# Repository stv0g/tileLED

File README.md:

tileLED
=======

A very minimalistic driver for 8x8 LED dot matrix displays.

Based on an ATmega8 this board can drive a simple LED matrix displays. There is no real "driver" circuit on the board. We just use the GPIOs of the AVR mcu to sink/source the LED current.

According to the ATmega8 datasheet this usage is a bit out of spec, but tests with 3 Volt button cells were successful. Also 5 Volt supplies are okay.

The source code includes a simple demonstration application. Paired with a DS1820 digital temperature sensor, the display shows the current temperature and records the minimal and maximal temperature ever measured.

A Blog post on http://www.steffenvogel.de will follow.

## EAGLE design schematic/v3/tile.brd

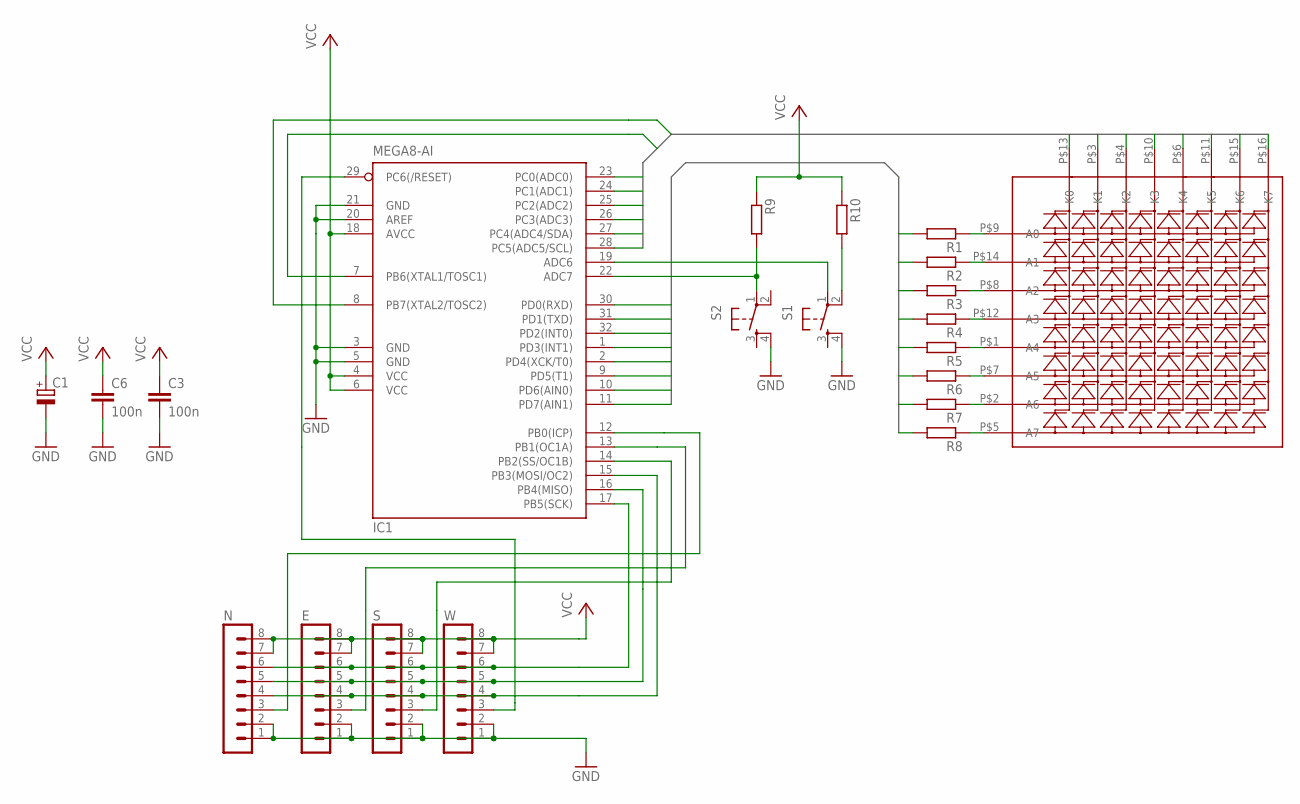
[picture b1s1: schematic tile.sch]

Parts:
C1: CPOL-EUB; PANASONIC_B
C3, C6: 100n; C0805
E: MA08-1
IC1: MEGA8-AI; TQFP32-08
N: MA08-1
R1, R2, R3, R4, R5, R6, R7, R8, R9, R10: R-EU_M0805; M0805
S: MA08-1
S1, S2: TAC_SWITCHSMD; TACTILE_SWITCH_SMD
U$1: LED-MATRIX
W: MA08-1

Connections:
A0: IC1.30 (PD0(RXD)), R1.2
A1: IC1.31 (PD1(TXD)), R2.2
A2: IC1.32 (PD2(INT0)), R3.2
A3: IC1.1 (PD3(INT1)), R4.2
A4: IC1.2 (PD4(XCK/T0)), R5.2
A5: IC1.9 (PD5(T1)), R6.2
A6: IC1.10 (PD6(AIN0)), R7.2
A7: IC1.11 (PD7(AIN1)), R8.2
GND: C1.-, C3.2, C6.2, E.1, E.2, IC1.3 (GND), IC1.5 (GND), IC1.20 (AREF), IC1.21 (GND), N.1, N.2, S.1, S.2, S1.4, S2.4, W.1, W.2
K0: IC1.23 (PC0(ADC0)), U$1.P$13 (K0)
K1: IC1.24 (PC1(ADC1)), U$1.P$3 (K1)
K2: IC1.25 (PC2(ADC2)), U$1.P$4 (K2)
K3: IC1.26 (PC3(ADC3)), U$1.P$10 (K3)
K4: IC1.27 (PC4(ADC4/SDA)), U$1.P$6 (K4)
K5: IC1.28 (PC5(ADC5/SCL)), U$1.P$11 (K5)
K6: IC1.7 (PB6(XTAL1/TOSC1)), U$1.P$15 (K6)
K7: IC1.8 (PB7(XTAL2/TOSC2)), U$1.P$16 (K7)
unnamed: IC1.19 (ADC6), S1.1
unnamed: IC1.22 (ADC7), R9.2, S2.1
unnamed: E.4, IC1.15 (PB3(MOSI/OC2)), N.4, S.4, W.4
unnamed: R10.2, S1.2
unnamed: IC1.14 (PB2(SS/OC1B)), S.3
unnamed: E.6, IC1.17 (PB5(SCK)), N.6, S.6, W.6
unnamed: IC1.29 (PC6(/RESET)), W.3
unnamed: E.5, IC1.16 (PB4(MISO)), N.5, S.5, W.5
unnamed: IC1.12 (PB0(ICP)), N.3
unnamed: E.3, IC1.13 (PB1(OC1A))
NA0: R1.1, U$1.P$9 (A0)
NA1: R2.1, U$1.P$14 (A1)
NA2: R3.1, U$1.P$8 (A2)
NA3: R4.1, U$1.P$12 (A3)
NA4: R5.1, U$1.P$1 (A4)
NA5: R6.1, U$1.P$7 (A5)
NA6: R7.1, U$1.P$2 (A6)
NA7: R8.1, U$1.P$5 (A7)
VCC: C1.+, C3.1, C6.1, E.7, E.8, IC1.4 (VCC), IC1.6 (VCC), IC1.18 (AVCC), N.7, N.8, R9.1, R10.1, S.7, S.8, W.7, W.8

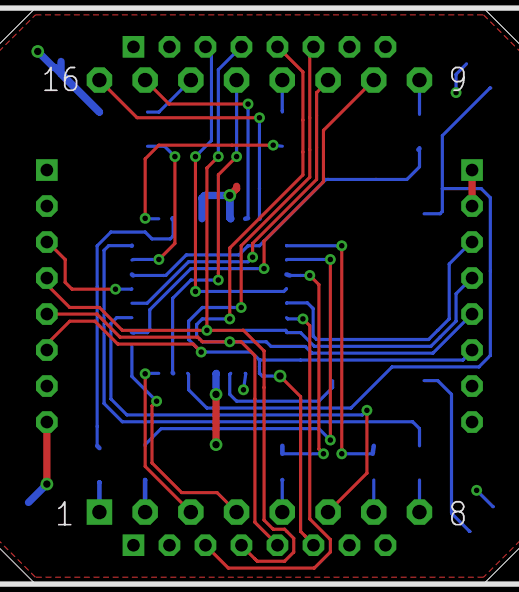
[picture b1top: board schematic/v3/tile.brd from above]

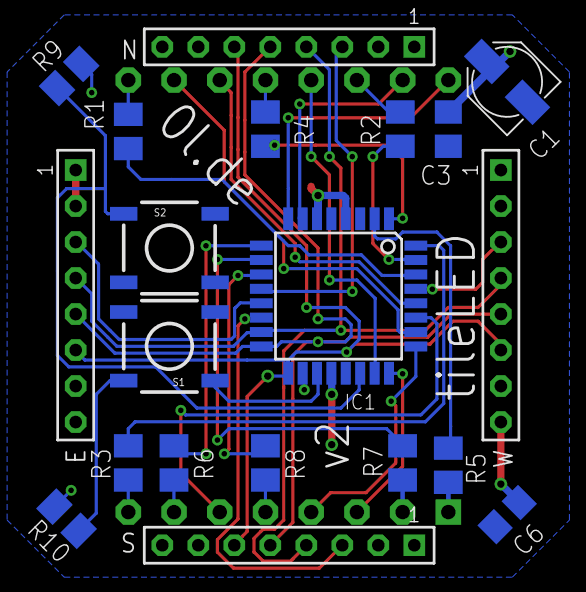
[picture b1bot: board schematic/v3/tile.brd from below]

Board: 2 copper layers, 21 parts (20 on the bottom side), 36 nets.

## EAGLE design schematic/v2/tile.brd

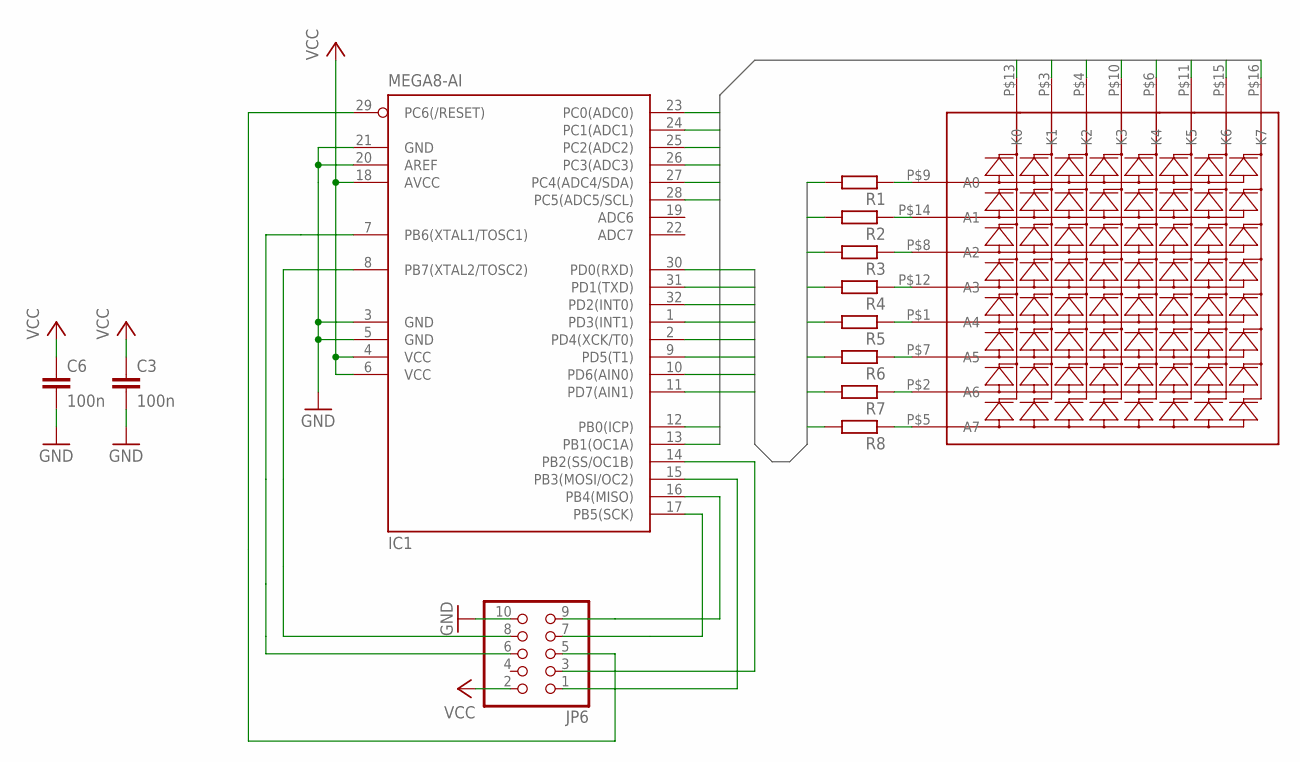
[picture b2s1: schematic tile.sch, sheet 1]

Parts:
C3, C6: 100n; C0805
IC1: MEGA8-AI; TQFP32-08
JP6: PINHD-2X5_2.54; 2X05
R1, R2, R3, R4, R5, R6, R7, R8: R-EU_M0805; M0805
U$1: LED-MATRIX

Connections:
A0: IC1.30 (PD0(RXD)), R1.1, R1.2, U$1.P$9 (A0)
A1: IC1.31 (PD1(TXD)), R2.1, R2.2, U$1.P$14 (A1)
A2: IC1.32 (PD2(INT0)), R3.1, R3.2, U$1.P$8 (A2)
A3: IC1.1 (PD3(INT1)), R4.1, R4.2, U$1.P$12 (A3)
A4: IC1.2 (PD4(XCK/T0)), R5.1, U$1.P$1 (A4)
A5: IC1.9 (PD5(T1)), R5.2, R6.1, R6.2, U$1.P$7 (A5)
A6: IC1.10 (PD6(AIN0)), R7.1, R7.2, U$1.P$2 (A6)
A7: IC1.11 (PD7(AIN1)), R8.1, R8.2, U$1.P$5 (A7)
GND: C3.2, C6.2, IC1.3 (GND), IC1.5 (GND), IC1.20 (AREF), IC1.21 (GND), JP6.10; also elsewhere on the board
K0: IC1.23 (PC0(ADC0)), U$1.P$13 (K0)
K1: IC1.24 (PC1(ADC1)), U$1.P$3 (K1)
K2: IC1.25 (PC2(ADC2)), U$1.P$4 (K2)
K3: IC1.26 (PC3(ADC3)), U$1.P$10 (K3)
K4: IC1.27 (PC4(ADC4/SDA)), U$1.P$6 (K4)
K5: IC1.28 (PC5(ADC5/SCL)), U$1.P$11 (K5)
K6: IC1.12 (PB0(ICP)), U$1.P$15 (K6)
K7: IC1.13 (PB1(OC1A)), U$1.P$16 (K7)
unnamed: IC1.17 (PB5(SCK)), JP6.7
unnamed: IC1.8 (PB7(XTAL2/TOSC2)), JP6.8
unnamed: IC1.29 (PC6(/RESET)), JP6.5
unnamed: IC1.14 (PB2(SS/OC1B)), JP6.3
unnamed: IC1.16 (PB4(MISO)), JP6.9
unnamed: IC1.15 (PB3(MOSI/OC2)), JP6.1
unnamed: IC1.7 (PB6(XTAL1/TOSC1)), JP6.6
VCC: C3.1, C6.1, IC1.4 (VCC), IC1.6 (VCC), IC1.18 (AVCC), JP6.2; also elsewhere on the board

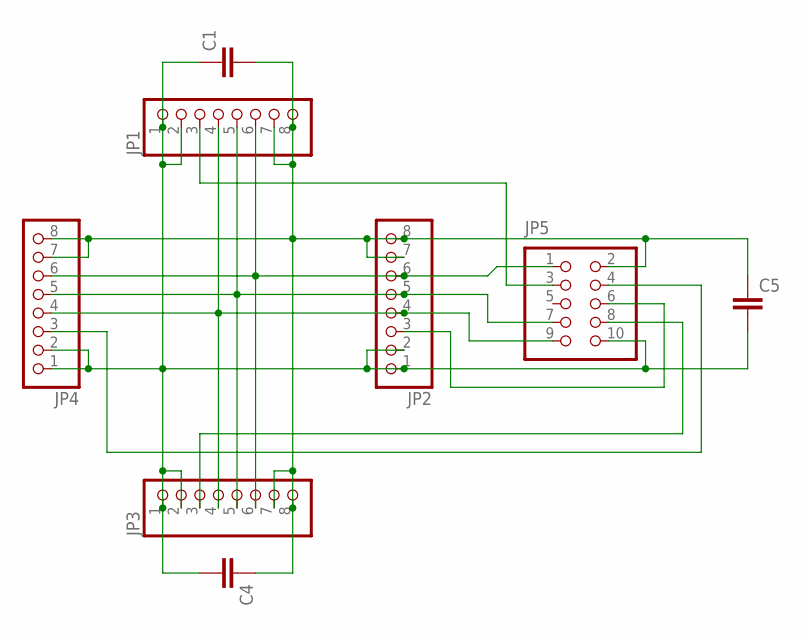
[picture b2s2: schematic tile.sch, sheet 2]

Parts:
C1, C4, C5: C-EUC0805; C0805
JP1, JP2, JP3, JP4: PINHD-1X8_2.00; 1X08M
JP5: PINHD-2X5_2.54; 2X05

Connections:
GND: C1.1, C4.2, C5.2, JP1.1, JP1.2, JP2.1, JP2.2, JP3.1, JP3.2, JP4.1, JP4.2, JP5.10; also elsewhere on the board
unnamed: JP4.3, JP5.4
unnamed: JP3.3, JP5.8
unnamed: JP2.3, JP5.6
unnamed: JP1.3, JP5.3
unnamed: JP1.6, JP2.6, JP3.6, JP4.6, JP5.1
unnamed: JP1.5, JP2.5, JP3.5, JP4.5, JP5.7
unnamed: JP1.4, JP2.4, JP3.4, JP4.4, JP5.9
VCC: C1.2, C4.1, C5.1, JP1.7, JP1.8, JP2.7, JP2.8, JP3.7, JP3.8, JP4.7, JP4.8, JP5.2; also elsewhere on the board

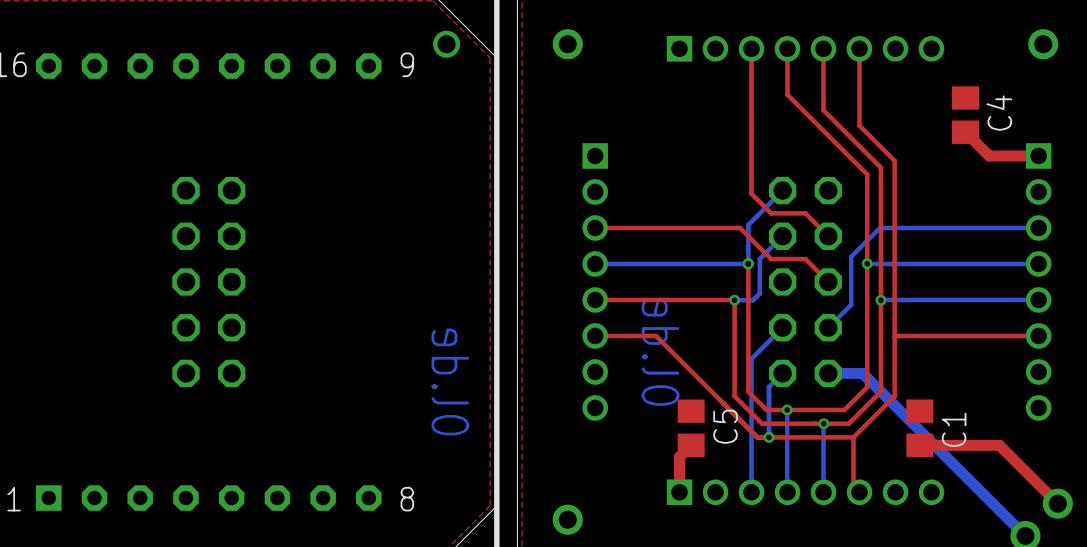
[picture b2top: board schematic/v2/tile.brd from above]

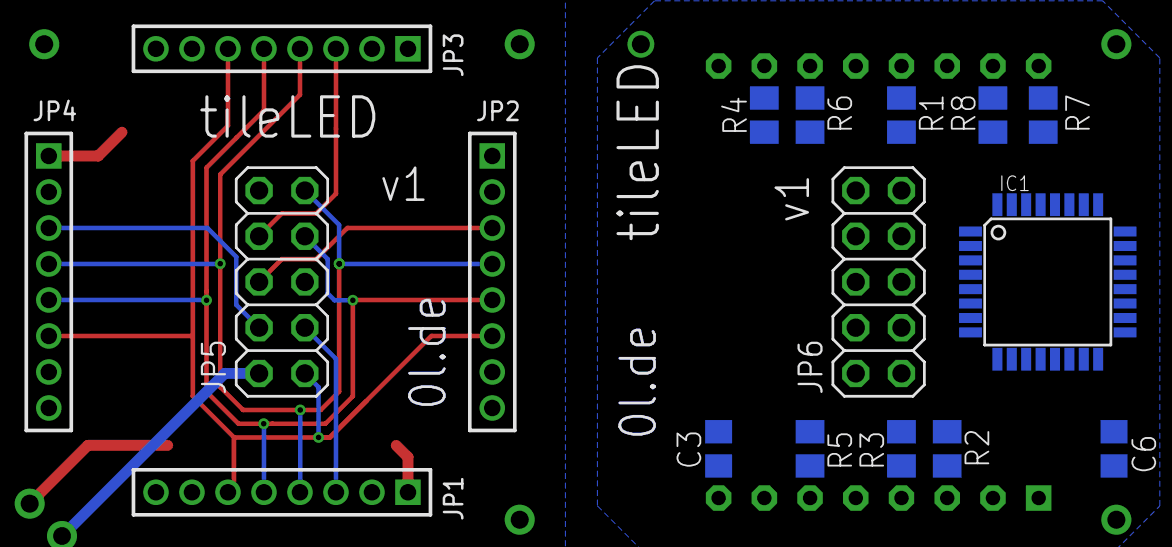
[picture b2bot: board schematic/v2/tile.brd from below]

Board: 2 copper layers, 21 parts (17 on the bottom side), 32 nets.

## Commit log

2014-01-04 added sourcecode
2014-01-04 added first schematic version
2014-01-04 added second schematic version
2014-01-04 added third schematic version
2014-01-04 added first thought about next gen hardware
2014-01-04 added gitignore file
2014-01-18 removed garbage
2014-01-18 updated gitignore and added note to fuses
2014-01-18 replaced Makefile by simpler one with fuse programming support

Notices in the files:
parts and their libraries:
SparkFun-Electromechanical: Licensing: CC v3.0 Share-Alike You are welcome to use this library for commercial purposes.
